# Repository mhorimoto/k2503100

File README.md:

# k2503100
リレーは使わない、SNMPだけ送信する＆Teensy4.1

## ディレクトリの説明

+ DOCS  
  設計に関する検討資料が含まれている。
+ KiCAD  
  KiCADによる回路設計の情報が含まれている。
  本装置はボタンスイッチを配置した基板が本体ケースの構成要素として大きな位置づけなので、
  本体ケースの製作に要する寸法図データもこのディレクトリに含めている。
+ PARTS_SPEC  
  製作に使用した部品の個別の仕様書やカタログが含まれている。
+ main  
  プログラムのソースコードが収められている。
  コンパイルなどはplatformIOを用いている。
+ snmp-manager  
  snmp-managerライブラリを用いた試験プログラムが収められている。普通は使わない。
+ snmp-test  
  snmp動作のテストプログラムが収められている。普通は使わない。
+ snmplib  
  snmpsetの動作確認用のプログラムが収められている。普通は使わない。
+ tools
  Ubuntu(Debian)系でplatformIOを使うときのudevruleファイルが収められている。

# CAUTION VERY IMPORTANT 重要な注意

PCB Revision 1.20まではLEDドライブ用のTrのフットパターンを間違えているので使わないように。

Don't use the wrong foot pattern of Tr for LED drive until PCB Revision 1.20.

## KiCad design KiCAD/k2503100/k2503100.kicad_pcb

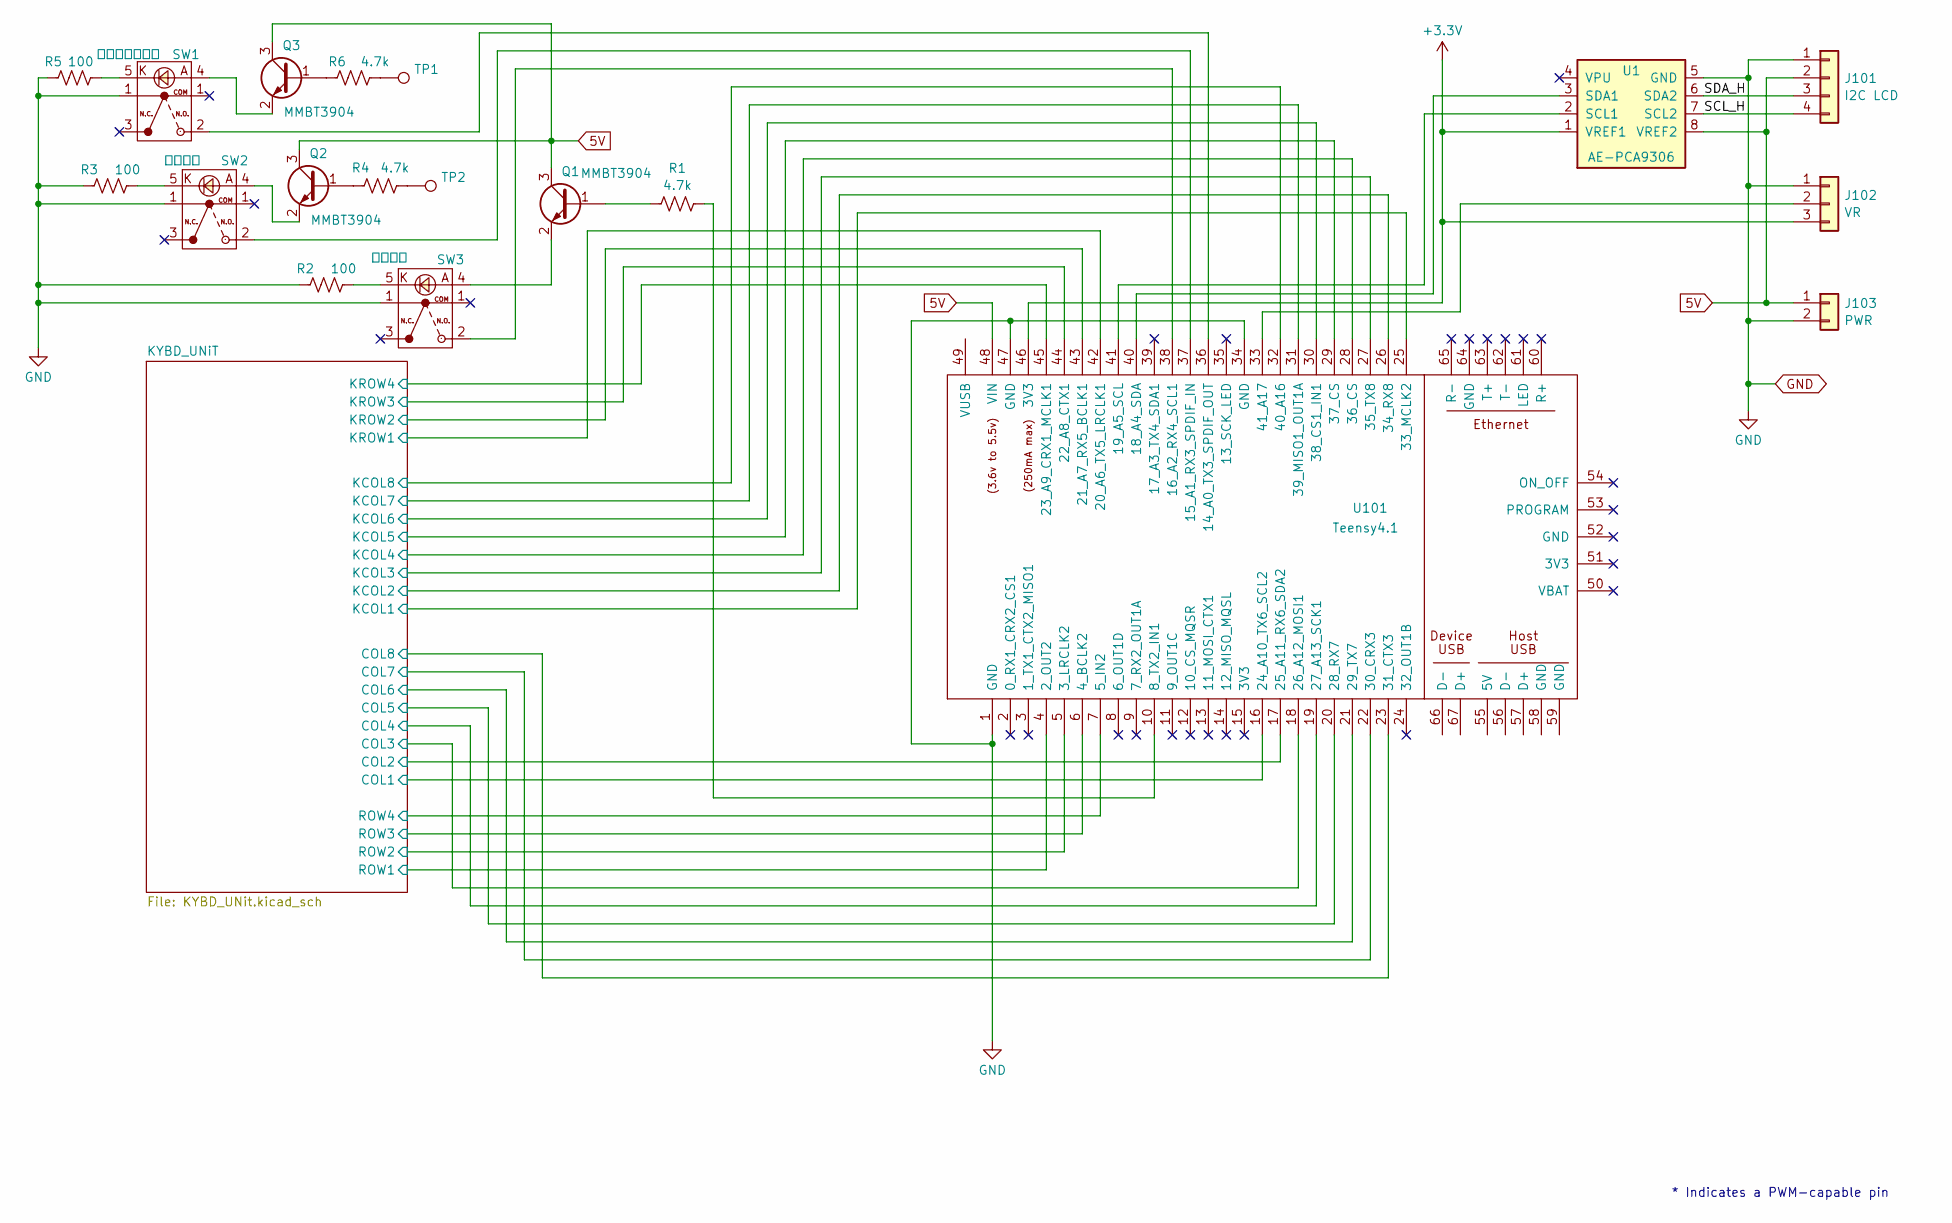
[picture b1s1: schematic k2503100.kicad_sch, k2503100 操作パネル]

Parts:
J101: I2C LCD; JST_XH_S4B-XH-A_1x04_P2.50mm_Horizontal
J102: VR; JST_XH_S3B-XH-A_1x03_P2.50mm_Horizontal
J103: PWR; JST_XH_S2B-XH-A_1x02_P2.50mm_Horizontal
Q1, Q2, Q3: MMBT3904; SOT-23
R1, R4, R6: 4.7k; R_0603_1608Metric_Pad0.98x0.95mm_HandSolder
R2, R3, R5: 100; R_0603_1608Metric_Pad0.98x0.95mm_HandSolder
SW1: サイレンテスト; MP86A1
SW2: 緊急停止; MP86A1
SW3: 放送開始; MP86A1
TP1, TP2: TestPoint; TestPoint_Pad_D2.0mm
U1: AE-PCA9306; DIP-8_W7.62mm
U101: Teensy4.1; Teensy41

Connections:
5V: J101.2, J103.1, Q1.3 (C), Q2.3 (C), Q3.3 (C), U1.8 (VREF2), U101.48 (VIN); also elsewhere on the board
+3.3V: J102.3, U1.1 (VREF1), U101.46 (3V3)
/KYBD_UNiT/COL1: U101.16 (24_A10_TX6_SCL2); also elsewhere on the board
/KYBD_UNiT/COL2: U101.17 (25_A11_RX6_SDA2); also elsewhere on the board
/KYBD_UNiT/COL3: U101.18 (26_A12_MOSI1); also elsewhere on the board
/KYBD_UNiT/COL4: U101.19 (27_A13_SCK1); also elsewhere on the board
/KYBD_UNiT/COL5: U101.20 (28_RX7); also elsewhere on the board
/KYBD_UNiT/COL6: U101.21 (29_TX7); also elsewhere on the board
/KYBD_UNiT/COL7: U101.22 (30_CRX3); also elsewhere on the board
/KYBD_UNiT/COL8: U101.23 (31_CTX3); also elsewhere on the board
/KYBD_UNiT/KCOL1: U101.25 (33_MCLK2); also elsewhere on the board
/KYBD_UNiT/KCOL2: U101.26 (34_RX8); also elsewhere on the board
/KYBD_UNiT/KCOL3: U101.27 (35_TX8); also elsewhere on the board
/KYBD_UNiT/KCOL4: U101.28 (36_CS); also elsewhere on the board
/KYBD_UNiT/KCOL5: U101.29 (37_CS); also elsewhere on the board
/KYBD_UNiT/KCOL6: U101.30 (38_CS1_IN1); also elsewhere on the board
/KYBD_UNiT/KCOL7: U101.31 (39_MISO1_OUT1A); also elsewhere on the board
/KYBD_UNiT/KCOL8: U101.32 (40_A16); also elsewhere on the board
/KYBD_UNiT/KROW1: U101.42 (20_A6_TX5_LRCLK1); also elsewhere on the board
/KYBD_UNiT/KROW2: U101.43 (21_A7_RX5_BCLK1); also elsewhere on the board
/KYBD_UNiT/KROW3: U101.44 (22_A8_CTX1); also elsewhere on the board
/KYBD_UNiT/KROW4: U101.45 (23_A9_CRX1_MCLK1); also elsewhere on the board
/KYBD_UNiT/ROW1: U101.4 (2_OUT2); also elsewhere on the board
/KYBD_UNiT/ROW2: U101.5 (3_LRCLK2); also elsewhere on the board
/KYBD_UNiT/ROW3: U101.6 (4_BCLK2); also elsewhere on the board
/KYBD_UNiT/ROW4: U101.7 (5_IN2); also elsewhere on the board
/SCL_H: J101.4, U1.7 (SCL2)
/SDA_H: J101.3, U1.6 (SDA2)
GND: J101.1, J102.1, J103.2, R2.2, R3.2, R5.2, SW1.1, SW2.1, SW3.1, U1.5 (GND), U101.1 (GND), U101.34 (GND), U101.47 (GND); also elsewhere on the board
unnamed: J102.2, U101.33 (41_A17)
unnamed: Q1.1 (B), R1.1
unnamed: Q1.2 (E), SW3.4
unnamed: Q2.1 (B), R4.1
unnamed: Q2.2 (E), SW2.4
unnamed: Q3.1 (B), R6.1
unnamed: Q3.2 (E), SW1.4
unnamed: R2.1, SW3.5
unnamed: R3.1, SW2.5
unnamed: R4.2, TP2.1
unnamed: R5.1, SW1.5
unnamed: R6.2, TP1.1
unnamed: U1.2 (SCL1), U101.41 (19_A5_SCL)
unnamed: U1.3 (SDA1), U101.40 (18_A4_SDA)
unnamed: R1.2, U101.10 (8_TX2_IN1)
unnamed: SW1.2, U101.36 (14_A0_TX3_SPDIF_OUT)
unnamed: SW2.2, U101.37 (15_A1_RX3_SPDIF_IN)
unnamed: SW3.2, U101.38 (16_A2_RX4_SCL1)

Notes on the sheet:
* Indicates a PWM-capable pin

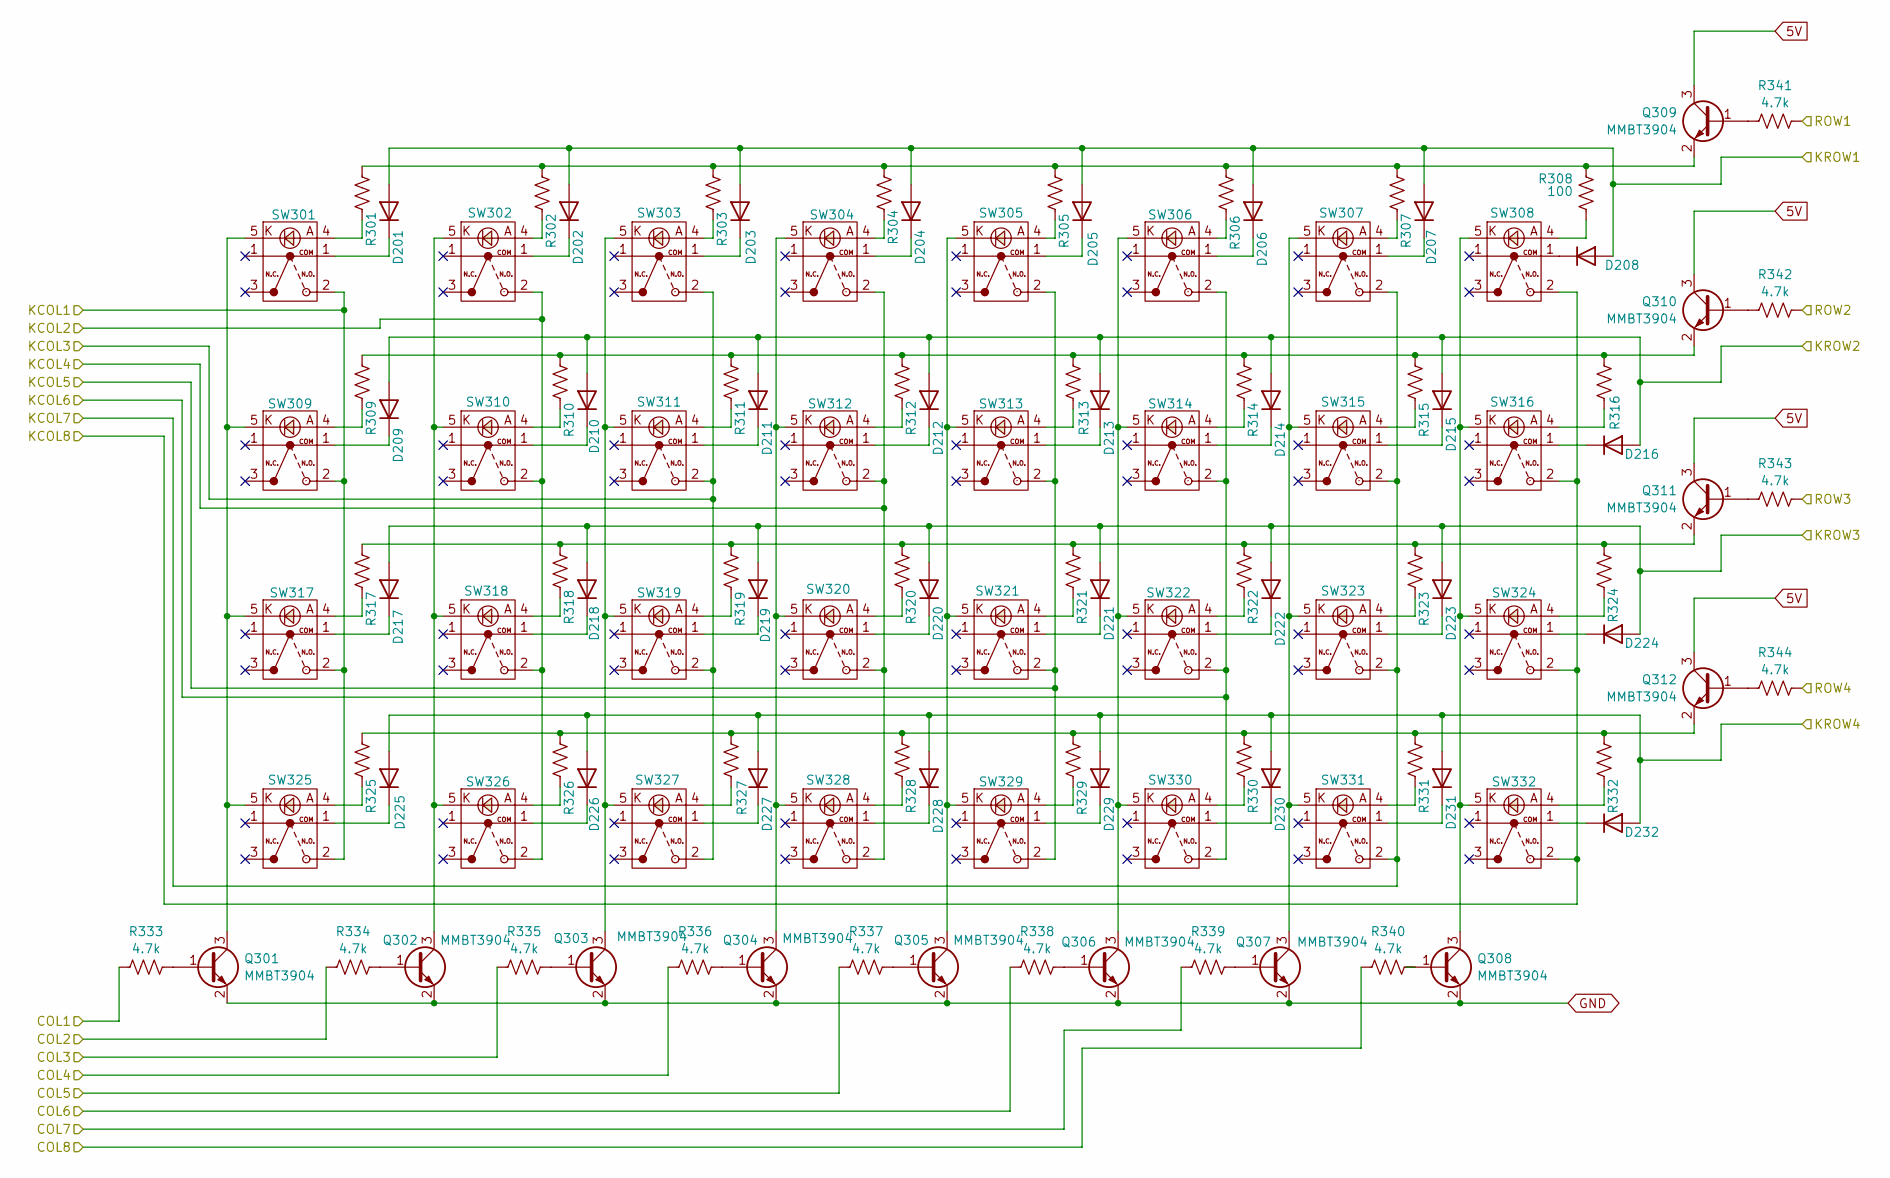
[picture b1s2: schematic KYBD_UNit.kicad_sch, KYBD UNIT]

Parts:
D201, D202, D203, D204, D205, D206, D207, D208, D209, D210, D211, D212, D213, D214, D215, D216, D217, D218, D219, D220, D221, D222, D223, D224, D225, D226, D227, D228, D229, D230, D231, D232: 1N4148W; D_SOD-123
Q301, Q302, Q303, Q304, Q305, Q306, Q307, Q308, Q309, Q310, Q311, Q312: MMBT3904; SOT-23
R301, R302, R303, R304, R305, R306, R307, R308, R309, R310, R311, R312, R313, R314, R315, R316, R317, R318, R319, R320, R321, R322, R323, R324, R325, R326, R327, R328, R329, R330, R331, R332: 100; R_0603_1608Metric_Pad0.98x0.95mm_HandSolder
R333, R334, R335, R336, R337, R338, R339, R340, R341, R342, R343, R344: 4.7k; R_0603_1608Metric_Pad0.98x0.95mm_HandSolder
SW301, SW302, SW303, SW304, SW305, SW306, SW307, SW308, SW309, SW310, SW311, SW312, SW313, SW314, SW315, SW316, SW317, SW318, SW319, SW320, SW321, SW322, SW323, SW324, SW325, SW326, SW327, SW328, SW329, SW330, SW331, SW332: MP86A1

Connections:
5V: Q309.3 (C), Q310.3 (C), Q311.3 (C), Q312.3 (C); also elsewhere on the board
/KYBD_UNiT/COL1: R333.1; also elsewhere on the board
/KYBD_UNiT/COL2: R334.1; also elsewhere on the board
/KYBD_UNiT/COL3: R335.1; also elsewhere on the board
/KYBD_UNiT/COL4: R336.1; also elsewhere on the board
/KYBD_UNiT/COL5: R337.1; also elsewhere on the board
/KYBD_UNiT/COL6: R338.1; also elsewhere on the board
/KYBD_UNiT/COL7: R339.1; also elsewhere on the board
/KYBD_UNiT/COL8: R340.1; also elsewhere on the board
/KYBD_UNiT/KCOL1: SW301.2, SW309.2, SW317.2, SW325.2; also elsewhere on the board
/KYBD_UNiT/KCOL2: SW302.2, SW310.2, SW318.2, SW326.2; also elsewhere on the board
/KYBD_UNiT/KCOL3: SW303.2, SW311.2, SW319.2, SW327.2; also elsewhere on the board
/KYBD_UNiT/KCOL4: SW304.2, SW312.2, SW320.2, SW328.2; also elsewhere on the board
/KYBD_UNiT/KCOL5: SW305.2, SW313.2, SW321.2, SW329.2; also elsewhere on the board
/KYBD_UNiT/KCOL6: SW306.2, SW314.2, SW322.2, SW330.2; also elsewhere on the board
/KYBD_UNiT/KCOL7: SW307.2, SW315.2, SW323.2, SW331.2; also elsewhere on the board
/KYBD_UNiT/KCOL8: SW308.2, SW316.2, SW324.2, SW332.2; also elsewhere on the board
/KYBD_UNiT/KROW1: D201.2 (A), D202.2 (A), D203.2 (A), D204.2 (A), D205.2 (A), D206.2 (A), D207.2 (A), D208.2 (A); also elsewhere on the board
/KYBD_UNiT/KROW2: D209.2 (A), D210.2 (A), D211.2 (A), D212.2 (A), D213.2 (A), D214.2 (A), D215.2 (A), D216.2 (A); also elsewhere on the board
/KYBD_UNiT/KROW3: D217.2 (A), D218.2 (A), D219.2 (A), D220.2 (A), D221.2 (A), D222.2 (A), D223.2 (A), D224.2 (A); also elsewhere on the board
/KYBD_UNiT/KROW4: D225.2 (A), D226.2 (A), D227.2 (A), D228.2 (A), D229.2 (A), D230.2 (A), D231.2 (A), D232.2 (A); also elsewhere on the board
/KYBD_UNiT/ROW1: R341.2; also elsewhere on the board
/KYBD_UNiT/ROW2: R342.2; also elsewhere on the board
/KYBD_UNiT/ROW3: R343.2; also elsewhere on the board
/KYBD_UNiT/ROW4: R344.2; also elsewhere on the board
GND: Q301.2 (E), Q302.2 (E), Q303.2 (E), Q304.2 (E), Q305.2 (E), Q306.2 (E), Q307.2 (E), Q308.2 (E); also elsewhere on the board
unnamed: D201.1 (K), SW301.1
unnamed: D202.1 (K), SW302.1
unnamed: D203.1 (K), SW303.1
unnamed: D204.1 (K), SW304.1
unnamed: D205.1 (K), SW305.1
unnamed: D206.1 (K), SW306.1
unnamed: D207.1 (K), SW307.1
unnamed: D208.1 (K), SW308.1
unnamed: D209.1 (K), SW309.1
unnamed: D210.1 (K), SW310.1
unnamed: D211.1 (K), SW311.1
unnamed: D212.1 (K), SW312.1
unnamed: D213.1 (K), SW313.1
unnamed: D214.1 (K), SW314.1
unnamed: D215.1 (K), SW315.1
unnamed: D216.1 (K), SW316.1
unnamed: D217.1 (K), SW317.1
unnamed: D218.1 (K), SW318.1
unnamed: D219.1 (K), SW319.1
unnamed: D220.1 (K), SW320.1
unnamed: D221.1 (K), SW321.1
unnamed: D222.1 (K), SW322.1
unnamed: D223.1 (K), SW323.1
unnamed: D224.1 (K), SW324.1
unnamed: D225.1 (K), SW325.1
unnamed: D226.1 (K), SW326.1
unnamed: D227.1 (K), SW327.1
unnamed: D228.1 (K), SW328.1
unnamed: D229.1 (K), SW329.1
unnamed: D230.1 (K), SW330.1
unnamed: D231.1 (K), SW331.1
unnamed: D232.1 (K), SW332.1
unnamed: Q301.1 (B), R333.2
unnamed: Q301.3 (C), SW301.5, SW309.5, SW317.5, SW325.5
unnamed: Q302.1 (B), R334.2
unnamed: Q302.3 (C), SW302.5, SW310.5, SW318.5, SW326.5
unnamed: Q303.1 (B), R335.2
unnamed: Q303.3 (C), SW303.5, SW311.5, SW319.5, SW327.5
unnamed: Q304.1 (B), R336.2
unnamed: Q304.3 (C), SW304.5, SW312.5, SW320.5, SW328.5
unnamed: Q305.1 (B), R337.2
unnamed: Q305.3 (C), SW305.5, SW313.5, SW321.5, SW329.5
unnamed: Q306.1 (B), R338.2
unnamed: Q306.3 (C), SW306.5, SW314.5, SW322.5, SW330.5
unnamed: Q307.1 (B), R339.2
unnamed: Q307.3 (C), SW307.5, SW315.5, SW323.5, SW331.5
unnamed: Q308.1 (B), R340.2
unnamed: Q308.3 (C), SW308.5, SW316.5, SW324.5, SW332.5
unnamed: Q309.1 (B), R341.1
unnamed: Q309.2 (E), R301.1, R302.1, R303.1, R304.1, R305.1, R306.1, R307.1, R308.1
unnamed: Q310.1 (B), R342.1
unnamed: Q310.2 (E), R309.1, R310.1, R311.1, R312.1, R313.1, R314.1, R315.1, R316.1
unnamed: Q311.1 (B), R343.1
unnamed: Q311.2 (E), R317.1, R318.1, R319.1, R320.1, R321.1, R322.1, R323.1, R324.1
unnamed: Q312.1 (B), R344.1
unnamed: Q312.2 (E), R325.1, R326.1, R327.1, R328.1, R329.1, R330.1, R331.1, R332.1
unnamed: R301.2, SW301.4
unnamed: R302.2, SW302.4
unnamed: R303.2, SW303.4
unnamed: R304.2, SW304.4
unnamed: R305.2, SW305.4
unnamed: R306.2, SW306.4
unnamed: R307.2, SW307.4
unnamed: R308.2, SW308.4
unnamed: R309.2, SW309.4
unnamed: R310.2, SW310.4
unnamed: R311.2, SW311.4
unnamed: R312.2, SW312.4
unnamed: R313.2, SW313.4
unnamed: R314.2, SW314.4
unnamed: R315.2, SW315.4
unnamed: R316.2, SW316.4
unnamed: R317.2, SW317.4
unnamed: R318.2, SW318.4
unnamed: R319.2, SW319.4
unnamed: R320.2, SW320.4
unnamed: R321.2, SW321.4
unnamed: R322.2, SW322.4
unnamed: R323.2, SW323.4
unnamed: R324.2, SW324.4
unnamed: R325.2, SW325.4
unnamed: R326.2, SW326.4
unnamed: R327.2, SW327.4
unnamed: R328.2, SW328.4
unnamed: R329.2, SW329.4
unnamed: R330.2, SW330.4
unnamed: R331.2, SW331.4
unnamed: R332.2, SW332.4

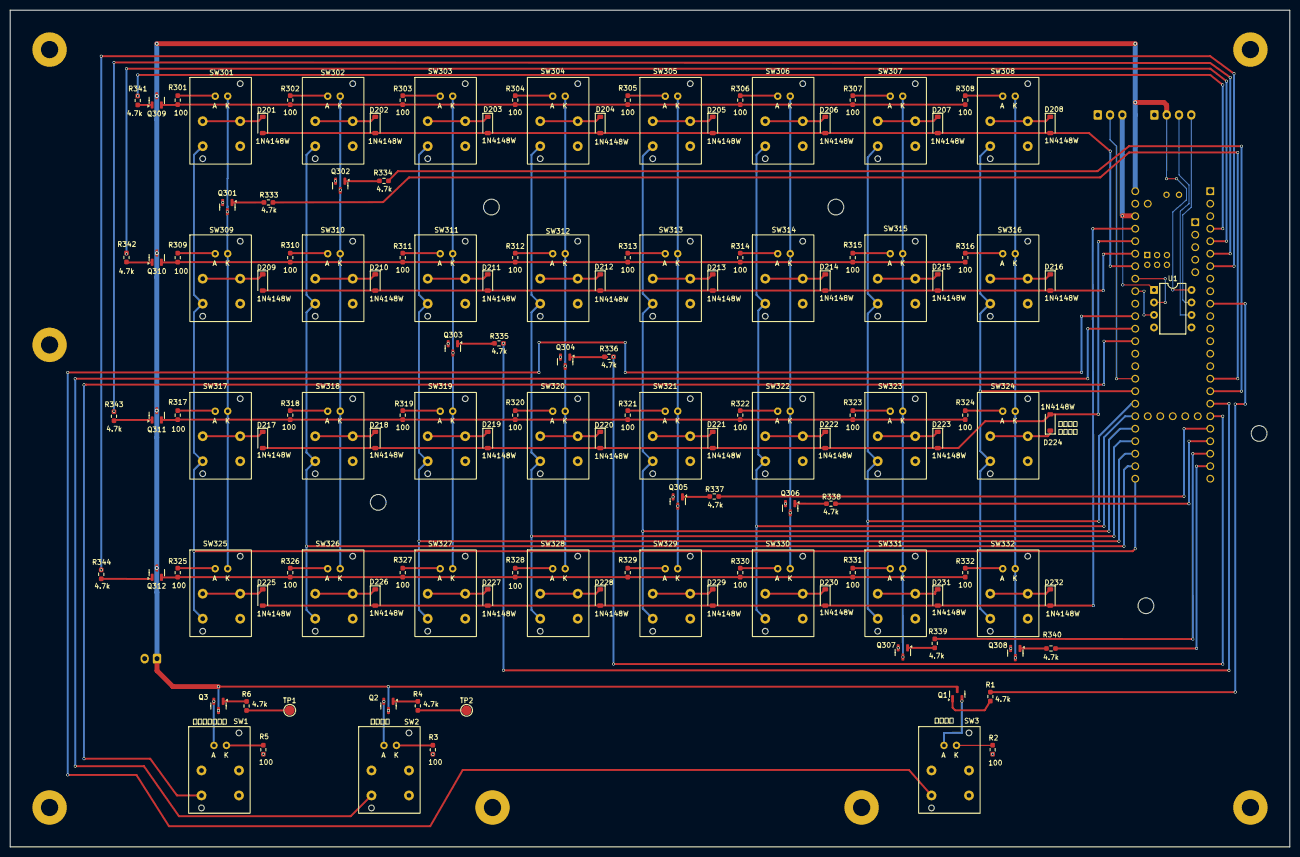
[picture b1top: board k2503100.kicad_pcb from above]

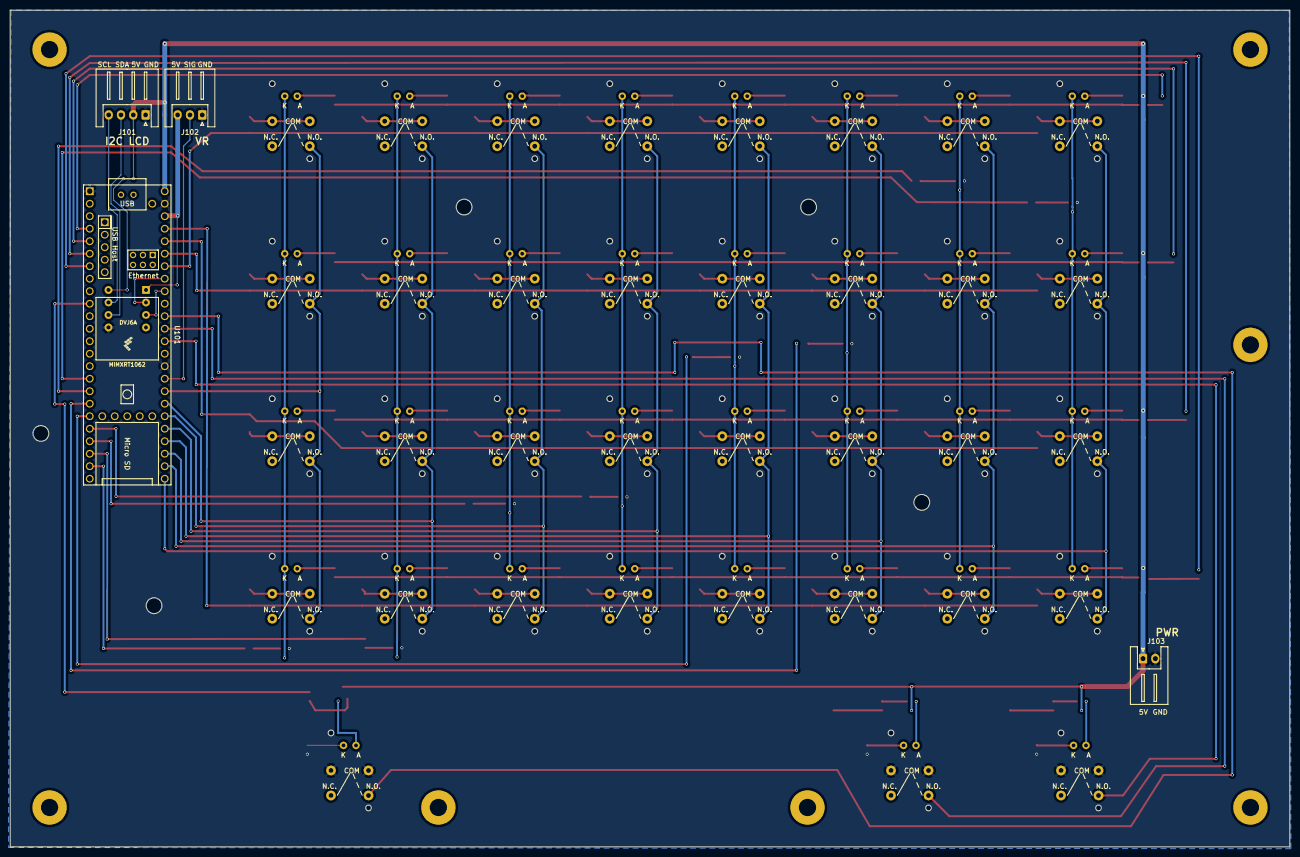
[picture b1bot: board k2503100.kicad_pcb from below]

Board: 2 copper layers, 260.0 x 170.0 mm, 139 parts (4 on the bottom side), 135 nets.

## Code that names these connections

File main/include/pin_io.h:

#define SW1 14
#define button_SIRENTEST 14
#define SW2 15
#define button_EMGSTOP 15
#define SW3 16
#define button_BROADCAST 16
#define VR  A17
#define COL1  24
#define COL2  25
#define COL3  26
#define COL4  27
#define COL5  28
#define COL6  29
#define COL7  30
#define COL8  31

#define ROW1  2
#define ROW2  3
#define ROW3  4
#define ROW4  5

#define LED_BROADCAST  8

#define KCOL1 33
#define KCOL2 34
#define KCOL3 35
#define KCOL4 36
#define KCOL5 37
#define KCOL6 38
#define KCOL7 39
#define KCOL8 40

#define KROW1 20
#define KROW2 21
#define KROW3 22
#define KROW4 23

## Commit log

2023-09-01 CAD: 1st
2023-09-15 Keyboard_UNiT記述中
2023-09-16 途中 Relay Unit
2023-09-18 Relay_UNiTの端子名入れ途中
2024-05-18 KiCAD 8
2024-05-23 設計資料作り
2024-05-24 tempfile purge
2024-05-24 説明文書構成図で遅延装置無し版を作成DIAGRAM02.pdf
2024-05-24 回路図にとりかかる
2024-06-06 append DOC
2024-07-02 SNMP and Teensy
2024-07-02 MP86A1のパーツ作成
2024-07-03 KYBD_UNit途中
2024-08-07 未使用回路の削除
2024-08-08 cont
2024-08-26 KCOL側配線途中
2024-08-27 KYBD UNIT ほぼ完成
2024-08-27 CPUとの接続途中
2024-09-25 DOCS:追加
2024-10-02 PDF作成
2024-10-04 Teensy tools の追加
2025-01-30 PCBデザイン開始
2025-01-31 PCB設計中
2025-01-31 マウントホール追加。I2Cなどを追加予定
2025-02-01 LCDとVRコネクタ追加
2025-02-01 寸法図途中
2025-02-02 スタッドを立てる位置はほぼ決まり。
2025-02-02 ケース加工用寸法線途中
2025-02-02 寸法線記入
2025-02-02 寸法線作業
2025-02-03 case設計
2025-02-04 PCB発注とソフト開発
2025-02-05 SNMPソフト開発中
2025-02-06 PCB製造開始
2025-02-07 POSファイル追加
2025-02-10 3DプリンタでRJ-45の留具を作るなど
2025-02-16 ソフト製作開始、mainの下でbutton14.cppなどを参考にしてる
2025-02-17 基板試作写真とソースコード編集中
2025-02-22 PCB 1.20まで（含む）は間違いなので使わない
2025-02-23 プログラム編集中、broadcast_flagの範囲がおかしい
2025-02-24 とりあえず動作確認版
2025-02-24 V0.16 STS1での1分間自動リセットの設定を行う
2025-03-03 ケース用寸法の追加
2025-03-24 MMBT3904に変更を開始
2025-03-25 MMBT3904変更済み
2025-03-25 Ver2.00
2025-03-28 MENU機能拡張手始め
